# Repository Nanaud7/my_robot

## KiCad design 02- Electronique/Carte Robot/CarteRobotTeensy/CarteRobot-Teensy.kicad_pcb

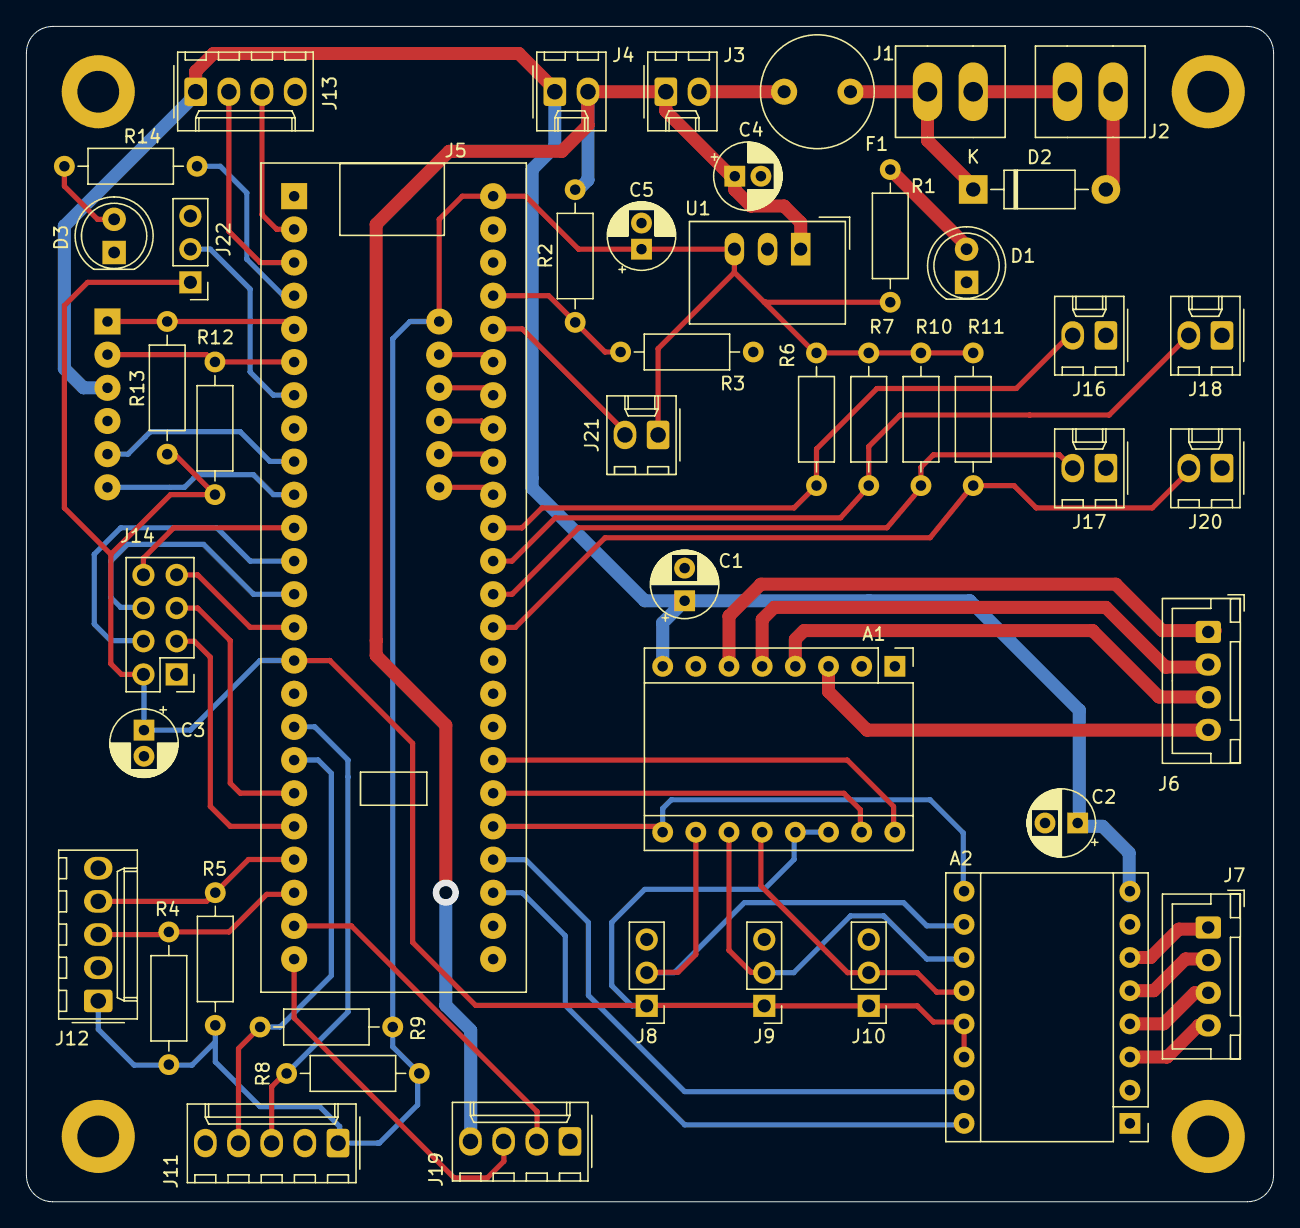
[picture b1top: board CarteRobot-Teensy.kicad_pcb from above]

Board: 2 copper layers, 95.5 x 90.0 mm, 52 parts (1 on the bottom side), 57 nets.

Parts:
A1, A2: Pololu_Breakout_DRV8825; Pololu_Breakout-16_15.2x20.3mm
C1, C2: 100u; CP_Radial_D5.0mm_P2.50mm
C3: 10u; CP_Radial_D5.0mm_P2.00mm
C4: 0,33u; CP_Radial_D5.0mm_P2.00mm
C5: 0,1u; CP_Radial_D5.0mm_P2.00mm
D1, D3: LED; LED_D5.0mm_Clear
D2: 1N4001; D_DO-41_SOD81_P10.16mm_Horizontal
F1: Fuse; Fuse_Littelfuse_372_D8.50mm
H1, H2, H3, H4: MountingHole; MountingHole_3.2mm_M3_DIN965_Pad
J1: Conn_Bat2; SL_3.50-02-180G_Weidmuller
J2: Conn_Bat1; SL_3.50-02-180G_Weidmuller
J3: Conn_OnOff; Molex_KK-254_AE-6410-02A_1x02_P2.54mm_Vertical
J4, J16, J17, J18, J20, J21: Conn_Aru; Molex_KK-254_AE-6410-02A_1x02_P2.54mm_Vertical
J5: Teensy-3.5; Teensy-3.5-3.6
J6: Conn_DriverD; JST_XH_B4B-XH-A_1x04_P2.50mm_Vertical
J7: Conn_DriverG; JST_XH_B4B-XH-A_1x04_P2.50mm_Vertical
J8, J9, J10, J22: Conn_01x03; PinHeader_1x03_P2.54mm_Vertical
J11, J12: Conn_01x05; Molex_KK-254_AE-6410-05A_1x05_P2.54mm_Vertical
J13: Conn_01x04; Molex_KK-254_AE-6410-04A_1x04_P2.54mm_Vertical
J14: Conn_02x04_Counter_Clockwise; PinHeader_2x04_P2.54mm_Vertical
J15: Shield-Actionneurs
J19: Conn_IHM; Molex_KK-254_AE-6410-04A_1x04_P2.54mm_Vertical
R1, R14: 500; R_Axial_DIN0207_L6.3mm_D2.5mm_P10.16mm_Horizontal
R2: 390k; R_Axial_DIN0207_L6.3mm_D2.5mm_P10.16mm_Horizontal
R3: 100k; R_Axial_DIN0207_L6.3mm_D2.5mm_P10.16mm_Horizontal
R4, R5, R8, R9, R12, R13: 4.7k; R_Axial_DIN0207_L6.3mm_D2.5mm_P10.16mm_Horizontal
R6, R7, R10, R11: 1k; R_Axial_DIN0207_L6.3mm_D2.5mm_P10.16mm_Horizontal
U1: TSR_1-2450; Converter_DCDC_TRACO_TSR-1_THT

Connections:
+3V3: A1.13, A1.14, A2.13, A2.14, C3.1, J5.15, J8.1, J9.1, J10.1, J14.2, J22.1, R12.1, R13.1
+5V: C5.1, J5.48, J11.1, J12.1, J15.7, J21.1, R1.1, R4.1, R5.1, R6.1, R7.1, R8.1, R9.1, R10.1, R11.1, U1.3
/17: J5.39, J15.12
/A1D: A1.4, J6.3
/A1G: A2.4, J7.3
/CE: J5.20, J14.3
/CODD_A: J5.22, J12.3, R4.2
/CODD_B: J5.21, J12.4, R5.2
/CODG_A: J5.17, J11.3, R8.2
/CODG_B: J5.18, J11.4, R9.2
/CS0: J5.12, J14.4
/DIR_D: A1.16, J5.31
/DIR_G: A2.16, J5.27
/EN: A1.9, A2.9, J5.29
/IRQ: J5.11, J14.8
/LED: J5.4, R14.1
/M0: A1.10, A2.10, J8.2
/M1: A1.11, A2.11, J9.2
/M2: A1.12, A2.12, J10.2
/MISO0: J5.14, J14.7
/MOSI0: J5.13, J14.6
/MS1: J5.38, J16.2, R6.2
/MS2: J5.37, J18.2, R7.2
/MS3: J5.36, J17.2, R10.2
/MS4: J5.35, J20.2, R11.2
/PWM1: J5.43, J15.8
/PWM2: J5.42, J15.9
/RX1: J5.2, J13.3
/RX3: J5.9, J15.5
/RX4: J5.23, J19.2
/SCK0: J5.19, J14.5
/SCL0: J5.41, J15.10
/SCL2: J5.5, J15.1, R13.2
/SDA0: J5.40, J15.11
/SDA2: J5.6, J15.2, R12.2
/STEP_D: A1.15, J5.30
/STEP_G: A2.15, J5.28
/STRAT: J5.7, J22.2
/TX1: J5.3, J13.2
/TX3: J5.10, J15.6
/TX4: J5.24, J19.3
/Tirette: J5.44, J21.2
/Varu: A1.8, A2.8, C1.1, C2.1, J4.1, J13.1, J15.3
/Vbat: J5.45, R2.2, R3.1
/Von: C4.1, J3.1, J4.2, J19.4, R2.1, U1.1
GND: A1.1, A1.7, A2.1, A2.7, C1.2, C2.2, C3.2, C4.2, C5.2, D1.1, D2.2, D3.1, J2.2, J5.1, J5.34, J8.3, J9.3, J10.3, J11.2, J11.5, J12.2, J12.5, J13.4, J14.1, J15.4, J16.1, J17.1, J18.1, J19.1, J20.1, J22.3, R3.2, U1.2
unnamed: A1.3, J6.4
unnamed: A1.5, J6.2
unnamed: A1.6, J6.1
unnamed: A2.3, J7.4
unnamed: A2.5, J7.2
unnamed: A2.6, J7.1
unnamed: D1.2, R1.2
unnamed: D2.1, F1.2, J1.1
unnamed: D3.2, R14.2
unnamed: F1.1, J3.2
unnamed: J1.2, J2.1

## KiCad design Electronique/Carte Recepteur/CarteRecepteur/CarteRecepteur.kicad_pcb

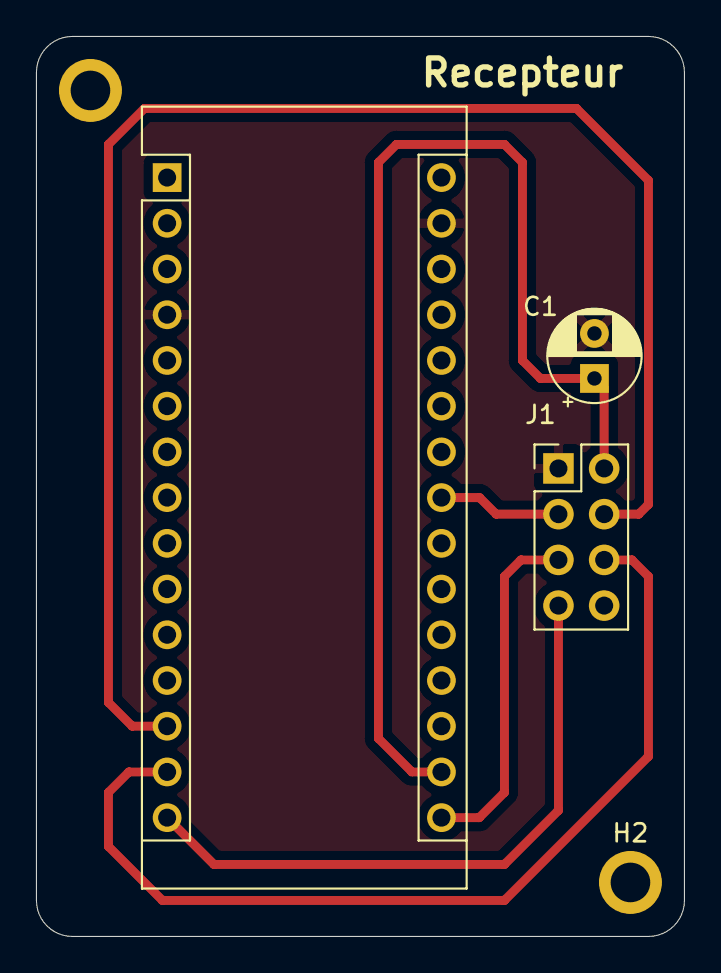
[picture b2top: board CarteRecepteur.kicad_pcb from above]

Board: 2 copper layers, 36.0 x 50.0 mm, 5 parts (0 on the bottom side), 7 nets.

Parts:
A1: Arduino_Nano_v3.x; Arduino_Nano
C1: CP1_Small; CP_Radial_D5.0mm_P2.50mm
H1, H2: MountingHole; MountingHole_2.2mm_M2_ISO7380_Pad
J1: Conn_02x04_Odd_Even_MountingPin; PinHeader_2x04_P2.54mm_Vertical

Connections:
+3V3: A1.17, C1.1, J1.2
/CE: A1.23, J1.3
/CS: A1.13, J1.4
/MISO: A1.15, J1.7
/MOSI: A1.14, J1.6
/SCK: A1.16, J1.5
GND: A1.4, A1.29, C1.2, J1.1

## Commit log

2021-07-17 Debut base roulante - chassis
2021-07-17 Bloc moteur
2021-07-17 Maj BOM Mecanique - Bloc moteurs
2021-07-17 codeur + piece pivot + support pivot
2021-07-18 roues + bloc codeur
2021-07-19 Support batterie
2021-07-21 support bille + modif chassis
2021-07-24 maj base roulante + ajout structure alu
2021-07-24 maj bom base roulante + bille en metal
2021-07-24 etages + maj bom
2021-07-25 changement dans le tri des pieces meca
2021-07-25 debut carte electronique base sur une Teensy
2021-07-26 maj schema de la carte robot
2021-07-27 ajout driver schema de la carte
2021-07-28 ajouts des connecteurs pour l'uart
2021-07-29 ajouts connecteurs, leds
2021-07-30 adaptateur servo Dynamixel + connecteur SPI
2021-07-31 Premiere version pcb
2021-07-31 correction structure mecanique
2021-08-01 modif elec + modif bom
2021-08-02 passage Teensy 3.5 + debut lidar
2021-08-03 maj bom + design piece lidar
2021-08-05 nouvelles pieces lidar
2021-08-07 modif elec + meca
2021-08-08 ajout des microrupteurs
2021-08-08 maj noms de fichiers meca
2021-08-14 creation projet sur platformIO
2021-08-14 routage pcb
2021-08-21 correction carte elec
2021-08-21 gerbers
2021-09-02 code ajout nRF
2021-09-04 test tipe
2021-09-07 creation projet recepteur
2021-09-09 ajout trous vis bloc moteurs chassis
2021-09-09 pcb recepteur
2021-09-09 support recepteur
2021-09-12 info recepteur
2021-09-12 modif Motor + creation Control
2021-09-13 Modif Control Rotation
2021-09-13 Definition des objectifs du projet
2021-09-13 ajout d'une FIFO pour le module nRF
2021-09-14 correction asserv
2021-09-14 asserv + strategie
2021-10-03 Suppression Features
2021-10-03 changement nommage dossiers principaux
2021-10-03 BOM déplacée dans gestion de projet
2021-10-03 test push
2021-10-03 Modif chassis + assemblage + lidar
2021-10-04 config code
2021-10-04 tige filetée
2021-10-05 travail ascenseur
2021-10-05 modif actionneurs
2021-10-10 debut conception ascenseur
2021-10-12 Export PCB Recepteur PDF
2021-10-13 changement rapides
2021-10-18 bcp de changements
2021-10-18 Maj ascenseur
2021-10-20 Modif support ascenseur
2021-10-21 Support batterie + Plaque ascenseur
2021-10-21 Modif support batterie 2
2021-10-21 Modif Base roulante + Ascenseur
2021-11-03 Modif noms fichiers + ascenseur
